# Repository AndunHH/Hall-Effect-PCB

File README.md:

# Hall-Effect-PCB
Repo to store PCB files for the hall effect sensor space mouse 

This repo is based on the work by Michael Roth:
https://www.printables.com/model/1063960-cad-mouse-spacemouse-using-hall-effect-sensors-w-p

Open the file in KiCad.

## Modifications
Added connectors for possible connection of keys, encoders and LEDs. The actual housing do not fit in a close space mouse, but it's fine for a first test or to solder the wires directly. 

Here a 3d rendering:

Here are the [STEP files](pcb.step) for the PCB itself.

Here a picture of the soldered PCB:

### Key Connector 1
16, 14, 15, 10 + GND + VCC 

### Key Connector 2
5, 7, 2, 3 + GND + VCC
(3 is doubled with LED!) -> solder connection point

### Encoder
VCC, GND, 0, 1

### LED strip
GND, VCC, 3  (3 is doubled with key!) -> solder connection point

# Part Library
This project uses the arduino pro micro KiCad part library by Biacco42:

https://github.com/Biacco42/ProMicroKiCad

Therefore it is included as a git submodul.

Please run `git submodule update --init` after cloning this repo in order to populate the folder on your disk.

# Create your own part

I strongly advise, that you open the part in the newest version of KiCad for yourself and check the designs. I used the plugin by Aisler to publish the files directly to their manufacturing service. The provided gerber files are therefore __untested__! 

[Gerber Files V1.zip](pcb/HallEffectPCB-v1-gerbers.zip)

Use them at your own risk!

Probably more resilient are those [ODB files](pcb/HallEffectPCB-v1-odb.zip).

# License 
Creative Commons License  

This work is licensed under a Creative Commons (4.0 International License)

Attribution—Noncommercial—Share Alike

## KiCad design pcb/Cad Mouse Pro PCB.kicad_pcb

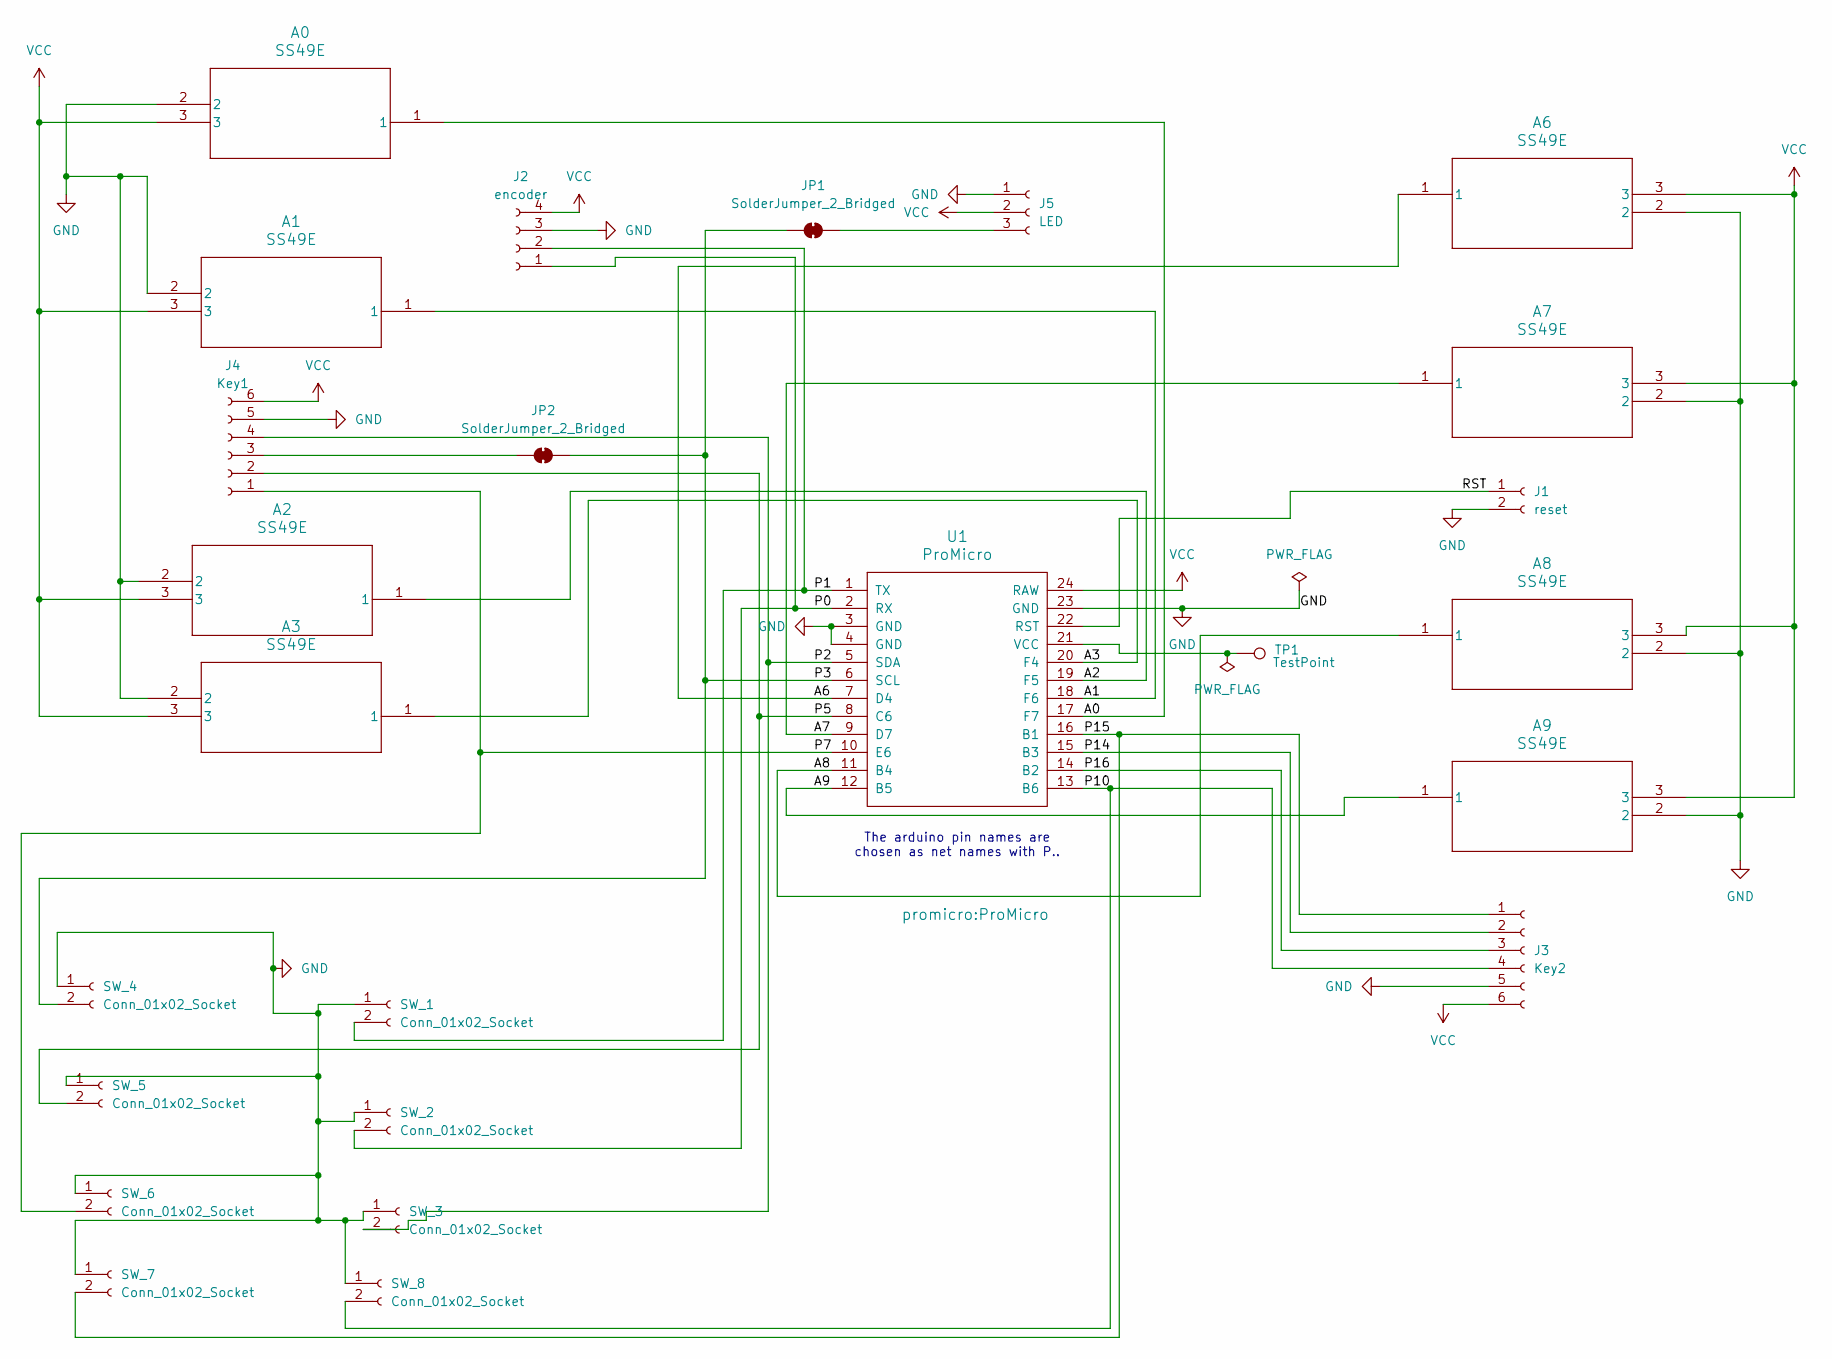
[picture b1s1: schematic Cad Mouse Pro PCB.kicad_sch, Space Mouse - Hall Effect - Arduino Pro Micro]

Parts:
A0, A1, A2, A3, A6, A7, A8, A9: SS49E; TO-92Flat
J1: reset; JST_XH_S2B-XH-A-1_1x02_P2.50mm_Horizontal
J2: encoder; JST_XH_S4B-XH-A-1_1x04_P2.50mm_Horizontal
J3: Key2; JST_XH_S6B-XH-A-1_1x06_P2.50mm_Horizontal
J4: Key1; JST_XH_S6B-XH-A-1_1x06_P2.50mm_Horizontal
J5: LED; JST_XH_S3B-XH-A-1_1x03_P2.50mm_Horizontal
JP1, JP2: SolderJumper_2_Bridged; SolderJumper-2_P1.3mm_Bridged2Bar_RoundedPad1.0x1.5mm
SW_1, SW_2, SW_3, SW_4, SW_5, SW_6, SW_7, SW_8: Conn_01x02_Socket; JST_ZH_B2B-ZR_1x02_P1.50mm_Vertical
TP1: TestPoint; TestPoint_Plated_Hole_D2.0mm
U1: ProMicro

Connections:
/A0: A0.1, U1.17 (F7)
/A1: A1.1, U1.18 (F6)
/A2: A2.1, U1.19 (F5)
/A3: A3.1, U1.20 (F4)
/A6: A6.1, U1.7 (D4)
/A7: A7.1, U1.9 (D7)
/A8: A8.1, U1.11 (B4)
/A9: A9.1, U1.12 (B5)
/P0: J2.1, SW_2.2, U1.2 (RX)
/P1: J2.2, SW_1.2, U1.1 (TX)
/P2: J4.4, SW_3.2, U1.5 (SDA)
/P3: JP1.2 (B), JP2.1 (A), SW_4.2, U1.6 (SCL)
/P5: J4.2, SW_5.2, U1.8 (C6)
/P7: J4.1, SW_6.2, U1.10 (E6)
/P10: J3.4, SW_8.2, U1.13 (B6)
/P14: J3.2, U1.15 (B3)
/P15: J3.1, SW_7.2, U1.16 (B1)
/P16: J3.3, U1.14 (B2)
/RST: J1.1, U1.22 (RST)
GND: A0.2, A1.2, A2.2, A3.2, A6.2, A7.2, A8.2, A9.2, J1.2, J2.3, J3.5, J4.5, J5.1, SW_1.1, SW_2.1, SW_3.1, SW_4.1, SW_5.1, SW_6.1, SW_7.1, SW_8.1, U1.3 (GND), U1.4 (GND), U1.23 (GND)
unnamed: J4.3, JP2.2 (B)
unnamed: J5.3, JP1.1 (A)
unnamed: TP1.1 (1_1), U1.21 (VCC)
VCC: A0.3, A1.3, A2.3, A3.3, A6.3, A7.3, A8.3, A9.3, J2.4, J3.6, J4.6, J5.2, U1.24 (RAW)

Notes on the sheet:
The arduino pin names are chosen as net names with P..

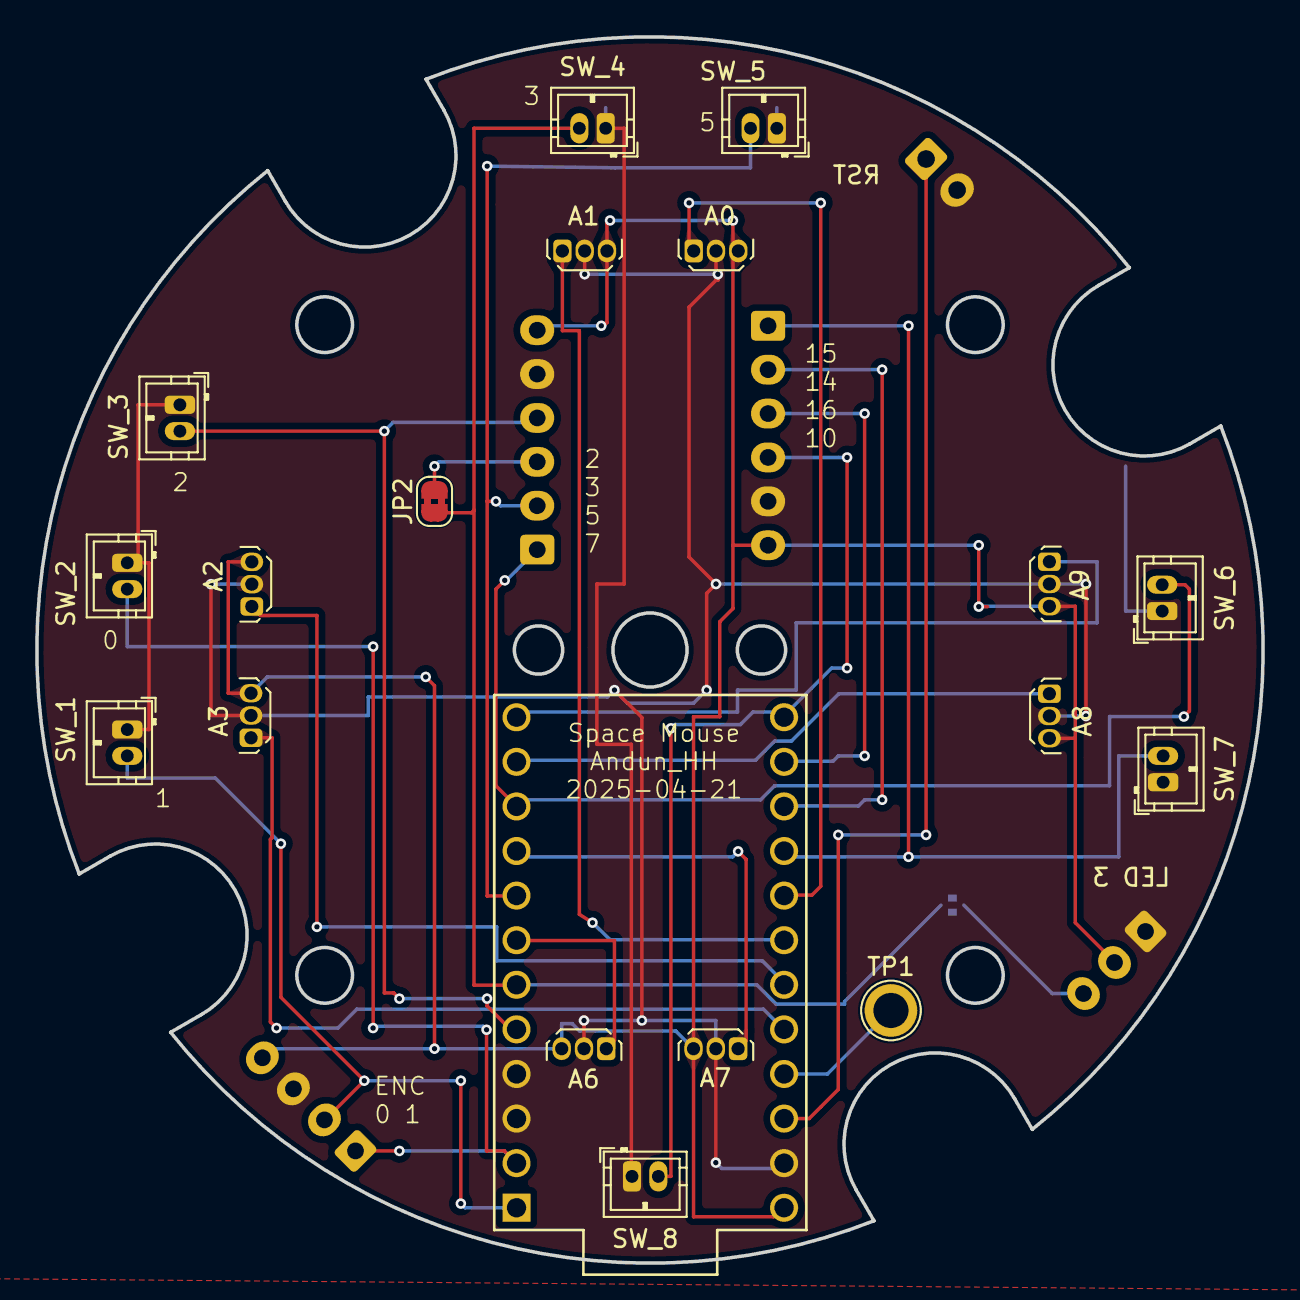
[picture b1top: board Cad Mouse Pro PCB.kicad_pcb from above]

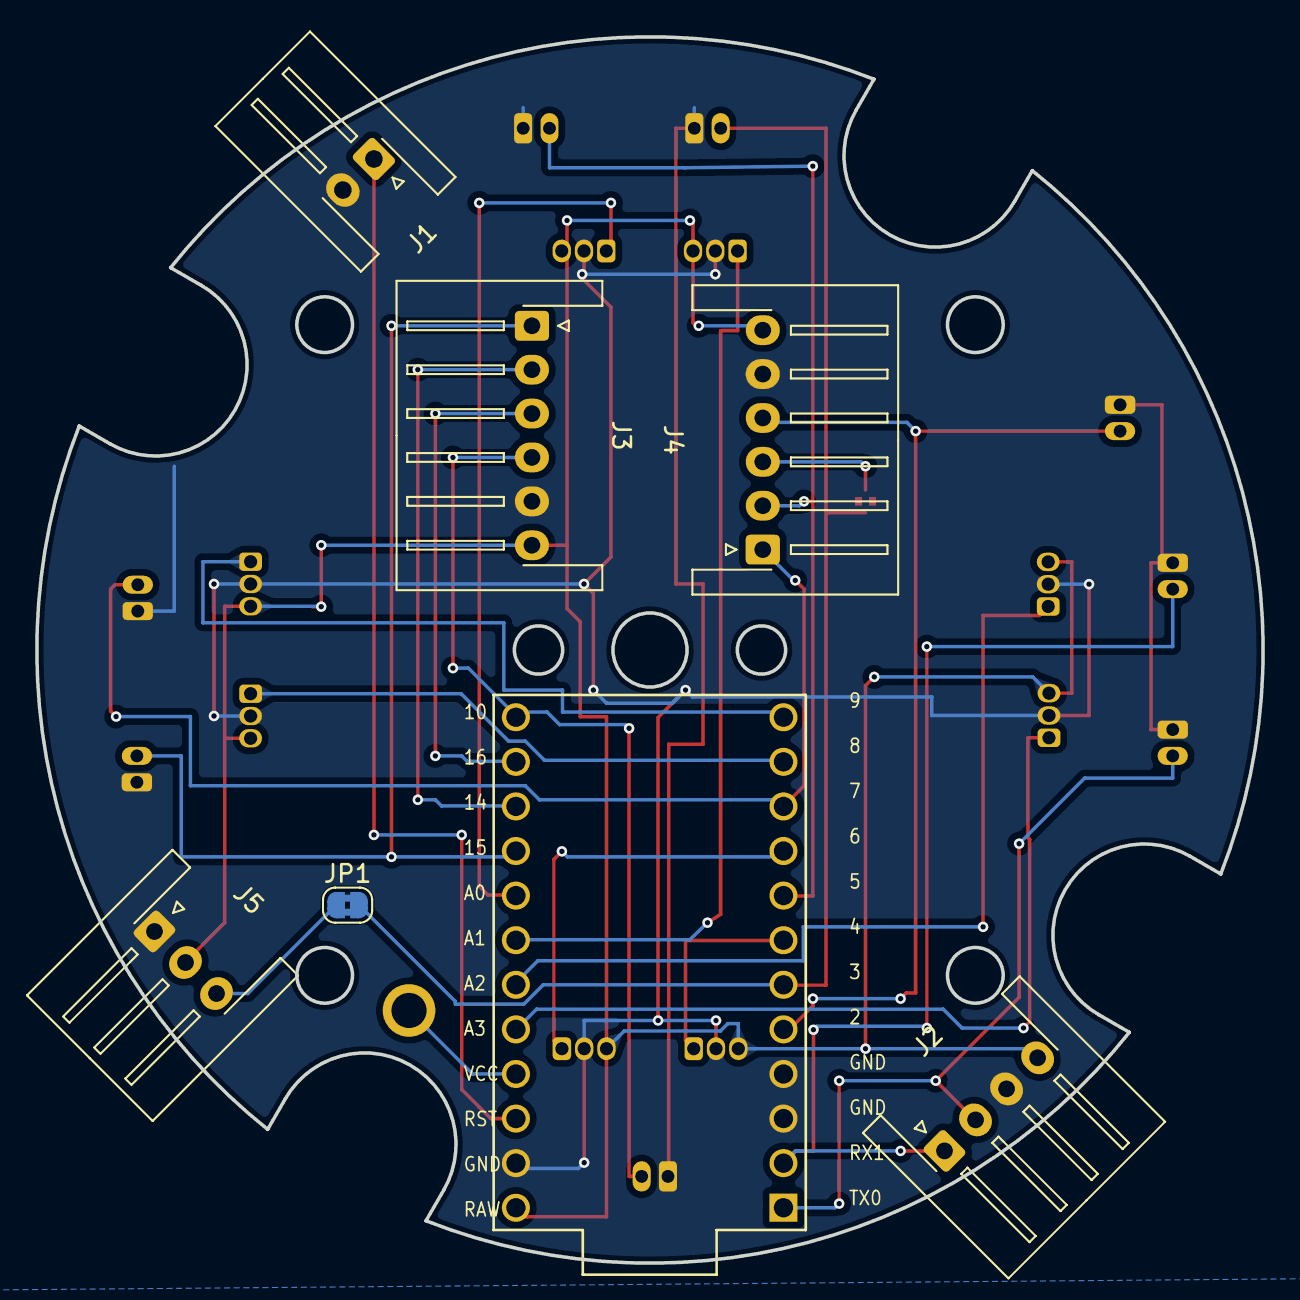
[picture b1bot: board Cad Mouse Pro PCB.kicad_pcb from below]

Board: 2 copper layers, 69.8 x 69.8 mm, 25 parts (7 on the bottom side), 24 nets.

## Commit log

2025-04-20 Init with M.Roths PCB
2025-04-21 Added pro micro submodul and connectors for debugging
2025-04-21 removed old files
2026-04-25 include odb and gerber files. untested!
